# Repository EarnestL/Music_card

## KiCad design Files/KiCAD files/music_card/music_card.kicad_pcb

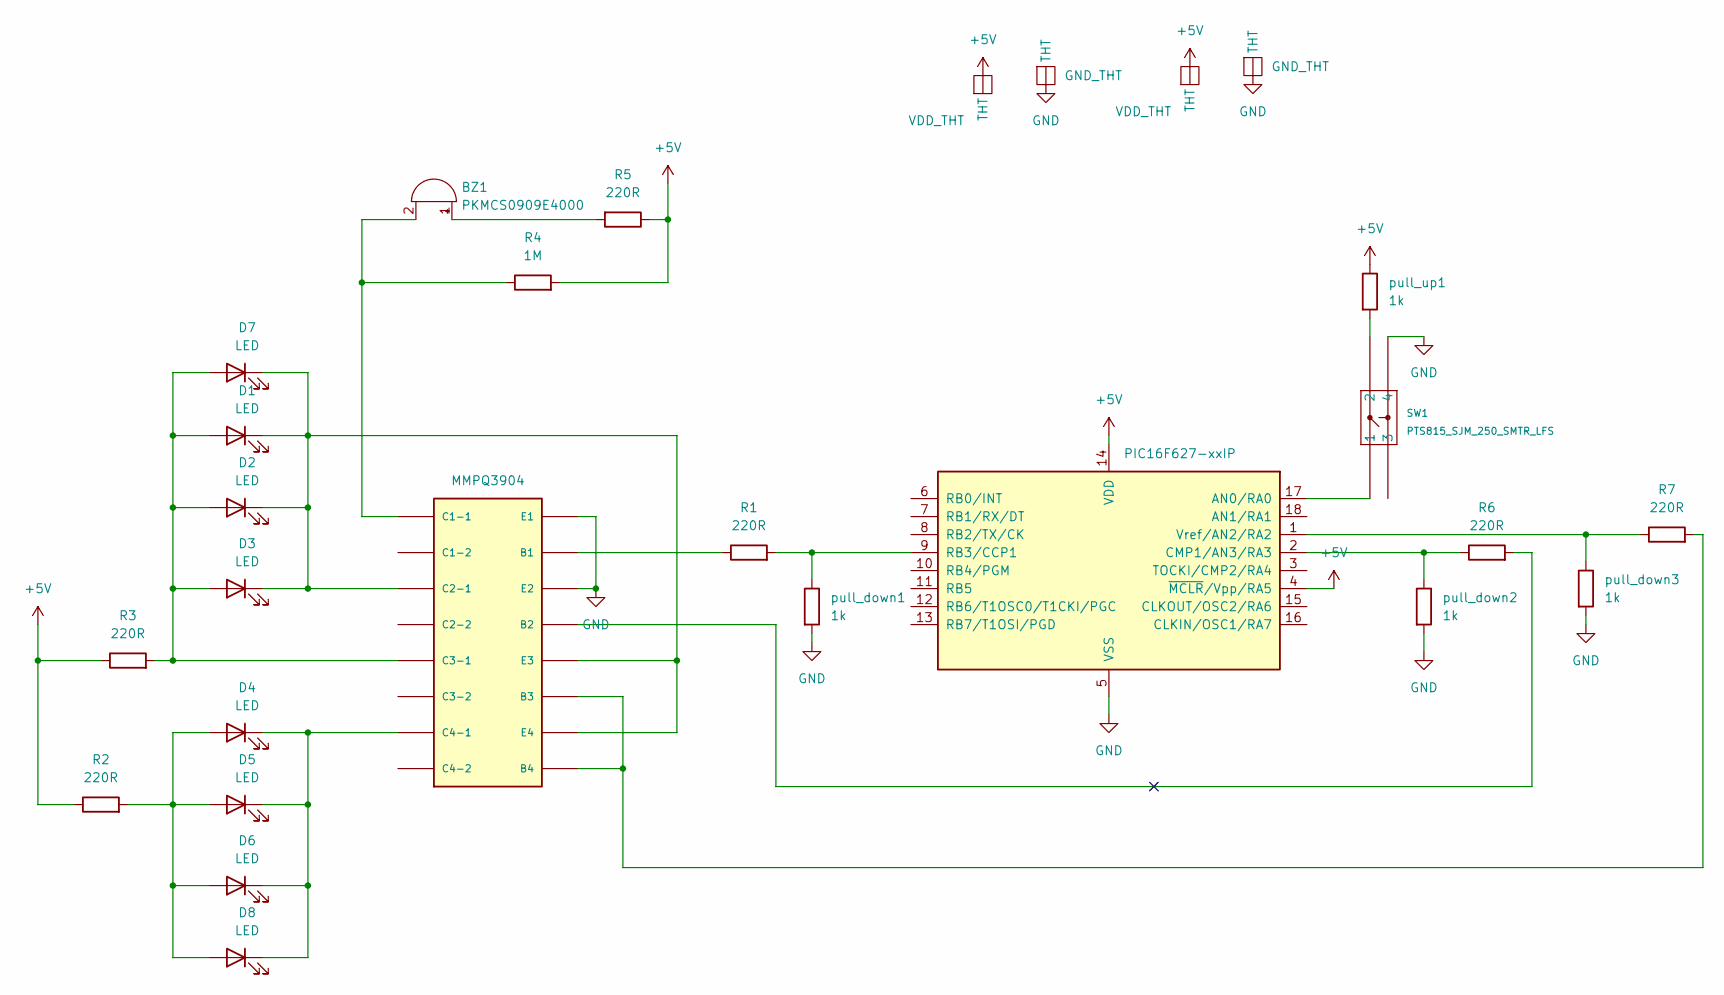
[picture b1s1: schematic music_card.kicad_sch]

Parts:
BZ1: PKMCS0909E4000; Buzzer_Murata_PKMCS0909E
D1, D2, D3, D4, D5, D6, D7, D8: LED; LED_0805_2012Metric_Pad1.15x1.40mm_HandSolder
GND_THT1, GND_THT2: GND_THT
R1, R2, R3, R5, R6, R7: 220R; R_0805_2012Metric_Pad1.20x1.40mm_HandSolder
R4: 1M; R_0805_2012Metric_Pad1.20x1.40mm_HandSolder
SW1: PTS815_SJM_250_SMTR_LFS; SW4_PTS815 SJM 250 SMTR LFS_CNK
U1: MMPQ3904; SOIC16_3P9X9P9_ONS
U2: PIC16F627-xxIP; DIP254P762X533-18
VDD_THT1, VDD_THT2: VDD_THT
pull_down1, pull_down2, pull_down3: 1k; R_0805_2012Metric_Pad1.20x1.40mm_HandSolder
pull_up1: 1k; R_0805_2012Metric_Pad1.20x1.40mm_HandSolder

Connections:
+5V: R2.1, R3.1, R4.2, R5.1, U2.4 (~MCLR/Vpp/RA5), U2.14 (VDD), VDD_THT1.1 (THT), VDD_THT2.1 (THT), pull_up1.1
GND: GND_THT1.1 (THT), GND_THT2.1 (THT), SW1.4, U1.14 (E2), U1.16 (E1), U2.5 (VSS), pull_down1.2, pull_down2.2, pull_down3.2
unnamed: BZ1.1 (-), R5.2
unnamed: BZ1.2 (+), R4.1, U1.1 (C1-1)
unnamed: D1.1 (K), D2.1 (K), D3.1 (K), D7.1 (K), U1.3 (C2-1), U1.10 (E4), U1.12 (E3)
unnamed: D1.2 (A), D2.2 (A), D3.2 (A), D7.2 (A), R3.2, U1.5 (C3-1)
unnamed: D4.1 (K), D5.1 (K), D6.1 (K), D8.1 (K), U1.7 (C4-1)
unnamed: D4.2 (A), D5.2 (A), D6.2 (A), D8.2 (A), R2.2
unnamed: R1.1, U1.15 (B1)
unnamed: R1.2, U2.9 (RB3/CCP1), pull_down1.1
unnamed: R6.1, U2.2 (CMP1/AN3/RA3), pull_down2.1
unnamed: R6.2, U1.13 (B2)
unnamed: R7.1, U2.1 (Vref/AN2/RA2), pull_down3.1
unnamed: R7.2, U1.9 (B4), U1.11 (B3)
unnamed: SW1.1, U2.17 (AN0/RA0)
unnamed: SW1.2, pull_up1.2

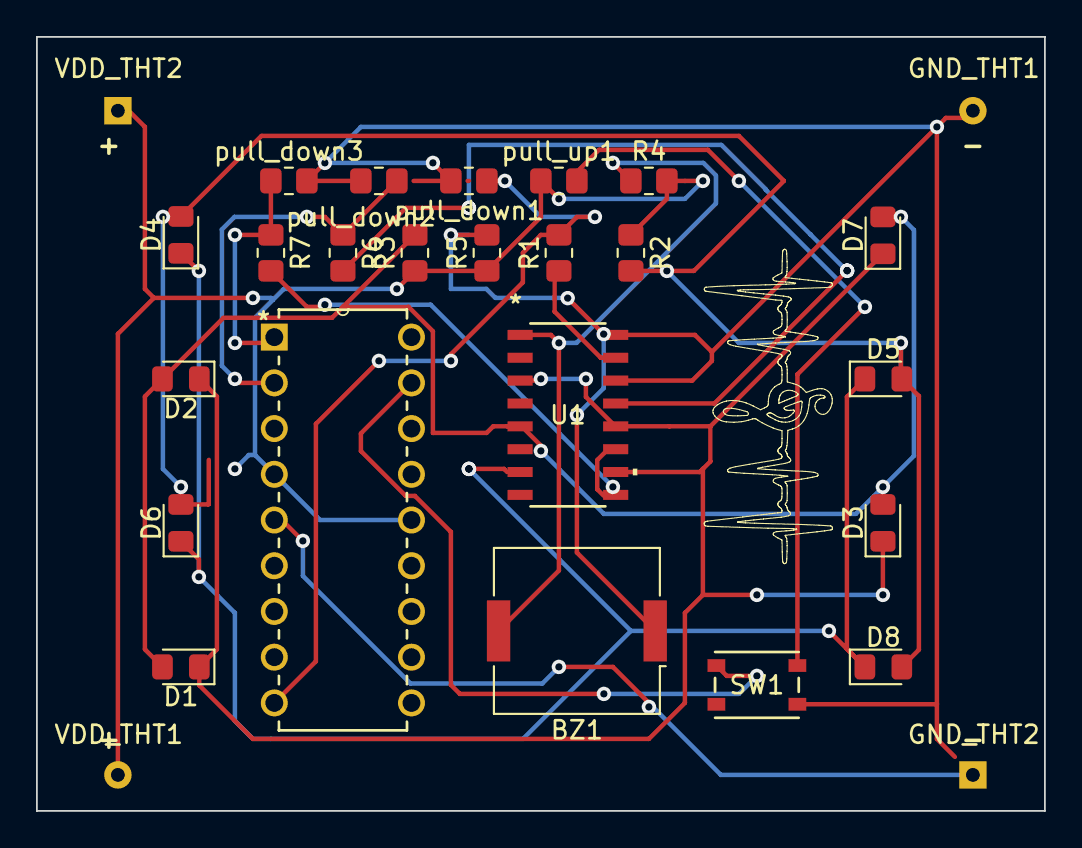
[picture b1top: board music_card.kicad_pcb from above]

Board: 2 copper layers, 56.0 x 43.0 mm, 27 parts (0 on the bottom side), 16 nets.

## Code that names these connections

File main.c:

/*
 * Author - Earnest Lin
 * Description - Sound card with flashing LEDs
 * Microcontroller - PIC16F627A
 */

// CONFIG
#pragma config FOSC = INTOSCIO  // Oscillator Selection bits (INTOSC oscillator: I/O function on RA6/OSC2/CLKOUT pin, I/O function on RA7/OSC1/CLKIN)
#pragma config WDTE = OFF       // Watchdog Timer Enable bit (WDT disabled)
#pragma config PWRTE = ON       // Power-up Timer Enable bit (PWRT enabled)
#pragma config MCLRE = OFF       // RA5/MCLR/VPP Pin Function Select bit (RA5/MCLR/VPP pin function is MCLR)
#pragma config BOREN = ON       // Brown-out Detect Enable bit (BOD enabled)
#pragma config LVP = OFF        // Low-Voltage Programming Enable bit (RB4/PGM pin has digital I/O function, HV on MCLR must be used for programming)
#pragma config CPD = OFF       // Data EE Memory Code Protection bit (Data memory code protection off)
#pragma config CP = OFF         // Flash Program Memory Code Protection bit (Code protection off)

#include <xc.h>
#include <pic16f627a.h>
#include <math.h>

// BITS DEF
#define BUTTON1 PORTAbits.RA0
#define LED_flash PORTAbits.RA2
#define LED_enable PORTAbits.RA3
#define BUZZER PORTBbits.RB3

// NOTE FREQUENCIES
#define null 10
#define G4	392.00
#define G4s 415.30
#define A4 440.00
#define A4s 466.16
#define B4	493.88
#define C5	523.25
#define C5s 554.37
#define D5 587.33
#define D5s 622.25
#define E5	659.25
#define F5	698.46
#define F5s 739.99
#define G5	783.99
#define G5s	830.61
#define A5	880.00
#define A5s 932.33
#define B5 987.77
#define C6 1046.50
#define C6s 1108.73
#define D6 1174.66
#define D6s 1244.51
#define E6 1318.51
#define F6 1396.91
#define F6s 1479.98
#define G6 1567.98
#define G6s 1661.22
#define A6 1760
#define A6s 1864.66
#define B6 1975.53
#define C7 2093
#define C7s 2217.46


// DUTY CYCLE
#define Percent 50

// OSC CLOCK SPEED
#define _XTAL_FREQ 4000000

//FUNCTION DECLARATION
void init();
void Freq_alt (int);
void delay_ms(unsigned int);
void buz_switch(int);

//TUNES
//HAPPY BIRTHDAY
const int hbd_array[29][2] = {{C6,350},{null,1},{C6,200},{D6,500},{C6,500},{F6,500},{E6,750}
                         ,{C6,350},{null,1},{C6,200},{D6,500},{C6,500},{G6,500},{F6,750}
                         ,{C6,350},{null,1},{C6,200},{C7s,500},{A6,500},{F6,500},{E6,550},{D6,650}
                         ,{A6s,350},{null,1},{A6s,200},{A6,500},{F6,500},{G6,500},{F6,1000}};
//PERFECT NIGHT
/*const int pn_array[45][2] = {{F6,200},{null,1},{F6,300},{null,1},{F6,200},{null,1},{A6,200},{null,1},
                        {F6,200},{null,1},{F6,300},{null,1},{F6,200},{null,1},{C6,200},{null,1},{C6,300},{null,1},
                        {C6,200},{null,1},{C6,200},{null,1},{G6,150},{null,1},{E6,200},{null,1},{E6,200},{null,1},
                        {E6,200},{null,1},{C6,200},{null,1},{C6,200},{null,1},{C6,200},{null,1},{C6,200},{null,1},
                        {G6,200},{null,1},{F6,200},{null,1},{E6,200},{null,1},{F6,800}};
*/
int size = sizeof(hbd_array)/sizeof(hbd_array[0]);

// MAIN
void main() {
    
    init();
    // Main loop begins
    while(1){
        
        if(BUTTON1 == 0){
            buz_switch(1); //sound on
            LED_enable = 1; // enable LEDs
        
            for (int i = 0; i < size; i++){ // play song and flash LEDs for each duration of notes
                LED_flash = ~LED_flash;
                Freq_alt(hbd_array[i][0]);
                delay_ms(hbd_array[i][1]);
            }
        
            LED_enable = 0; // disable LEDs
            buz_switch(0); //sound off
        }
    }
    return;
};


// Function definition
void init(){
    // Configure the comparator
    // Comparator module is turned off and used as I/O pins
    CMCONbits.CM = 0b111; // Turn off the comparator
    CMCONbits.CIS = 0; // Set the input to C1Vin-
    CMCONbits.C1INV = 0; // Output polarity is non-inverted
    CMCONbits.C2INV = 0; // Output polarity is non-inverted

    // Set IO pins
    TRISA0 = 1;
    TRISA2 = 0;
    TRISA3 = 0;
    
    // PWM configuration and frequency initialization
    TRISB3 = 0; //enable output for PWM
    T2CON = 0b00000110;  //enable timer 2 + prescaler value 16
    Freq_alt(0);
};

// Function definition
void Freq_alt(int x){
    
    PR2 = (uint8_t)(((4000000)/(16*x))-1); //period of PWM is written to PR2
    
    uint8_t duty_cycle = (uint8_t)((Percent*PR2)/100); //calculate duty cycle
    
    CCPR1L = duty_cycle >> 2; //Duty cycle is written to CCPR1L (contains the high 8 bits)
};

// Function definition
// cannot use __delay_ms() directly as it only takes constant parameter
void delay_ms(unsigned int ms){
    
   while(ms > 0){
       __delay_ms(1);
      ms--;
    }
 };

void buz_switch(int x){
    if (x){
        CCP1CONbits.CCP1M = 0b1100; // enable PWM
    }
    else{
        CCP1CONbits.CCP1M = 0b0000; // disable PWM
    };
    
};

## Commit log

2024-01-15 init
2024-01-15 build
2024-01-17 Gerber update
2024-01-28 Files Update
2024-01-28 vid update
2024-01-28 img1 update
2024-02-21 resize img1
